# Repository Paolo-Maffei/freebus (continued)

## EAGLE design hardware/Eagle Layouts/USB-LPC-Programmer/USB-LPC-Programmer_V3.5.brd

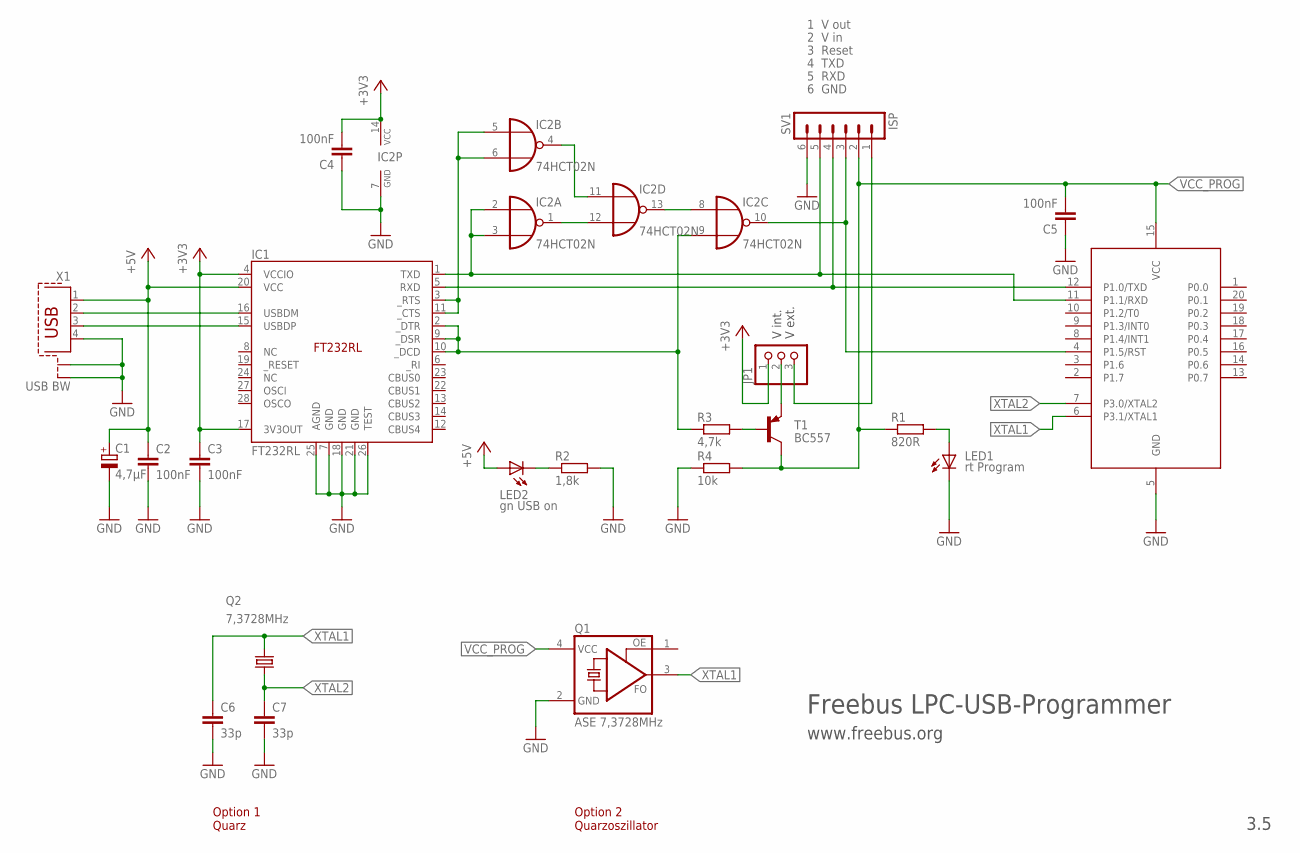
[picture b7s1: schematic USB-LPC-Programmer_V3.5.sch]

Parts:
89LPC922: LPC-Sockel; DIL20
C1: 4,7µF; E2,5-6
C2, C3, C4, C5: 100nF; C050-024X044
C6, C7: 33p; C025-024X044
IC1: FT232RL; SSOP-28
IC2: 74HCT02N; DIL14
JP1: PINHD-1X3; 1X03
LED1: rt Program; LED3MM
LED2: gn USB on; LED3MM
Q1: ASE 7,3728MHz; ASF
Q2: 7,3728MHz; HC49/S
R1: 820R; 0207/7
R2: 1,8k; 0207/7
R3: 4,7k; 0204/7
R4: 10k; 0207/7
SV1: ISP; MA06-1
T1: BC557; TO92
X1: USB BW; PN61729-S

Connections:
+3V3: C3.1, C4.2, IC1.4 (VCCIO), IC1.17 (3V3OUT), IC2.14 (VCC), JP1.1
+5V: C1.+, C2.1, IC1.20 (VCC), LED2.A, X1.1
GND: 89LPC922.5 (GND), C1.-, C2.2, C3.2, C4.1, C5.1, C6.2, C7.2, IC1.7 (GND), IC1.18 (GND), IC1.21 (GND), IC1.25 (AGND), IC1.26 (TEST), IC2.7 (GND), LED1.K (C), Q1.2 (GND), R2.2, R4.1, SV1.6, X1.4, X1.S1, X1.S2
unnamed: IC2.4 (O), IC2.11 (I0)
unnamed: JP1.2, T1.1 (E)
unnamed: 89LPC922.4 (P1.5/RST), IC2.10 (O), SV1.3
unnamed: JP1.3, SV1.1
unnamed: LED2.K (C), R2.1
unnamed: IC2.1 (O), IC2.12 (I1)
unnamed: LED1.A, R1.2
unnamed: IC1.16 (USBDM), X1.2
unnamed: IC2.8 (I0), IC2.13 (O)
unnamed: IC1.15 (USBDP), X1.3
unnamed: R3.2, T1.2 (B)
PROG_PWR_ON: IC1.2 (_DTR), IC1.9 (_DSR), IC1.10 (_DCD), IC2.9 (I1), R3.1
RTS_CTS1: IC1.3 (_RTS), IC1.11 (_CTS), IC2.5 (I0), IC2.6 (I1)
USB_RX: 89LPC922.12 (P1.0/TXD), IC1.5 (RXD), SV1.4
USB_TX: 89LPC922.11 (P1.1/RXD), IC1.1 (TXD), IC2.2 (I0), IC2.3 (I1), SV1.5
VCC_PROG: 89LPC922.15 (VCC), C5.2, Q1.4 (VCC), R1.1, R4.2, SV1.2, T1.3 (C)
XTAL1: 89LPC922.6 (P3.1/XTAL1), C6.1, Q1.3 (FO), Q2.2
XTAL2: 89LPC922.7 (P3.0/XTAL2), C7.1, Q2.1

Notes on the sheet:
Freebus LPC-USB-Programmer
www.freebus.org
3.5
2 V in
3 Reset
4 TXD
5 RXD
6 GND
1 V out
Option 1 Quarz
Option 2 Quarzoszillator
V int.
V ext.

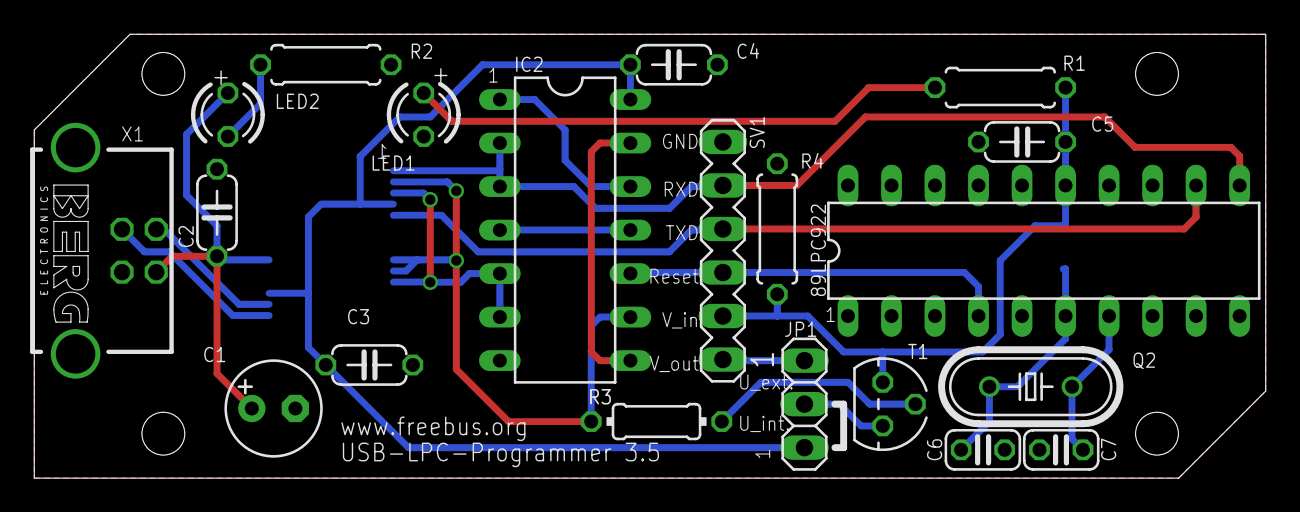
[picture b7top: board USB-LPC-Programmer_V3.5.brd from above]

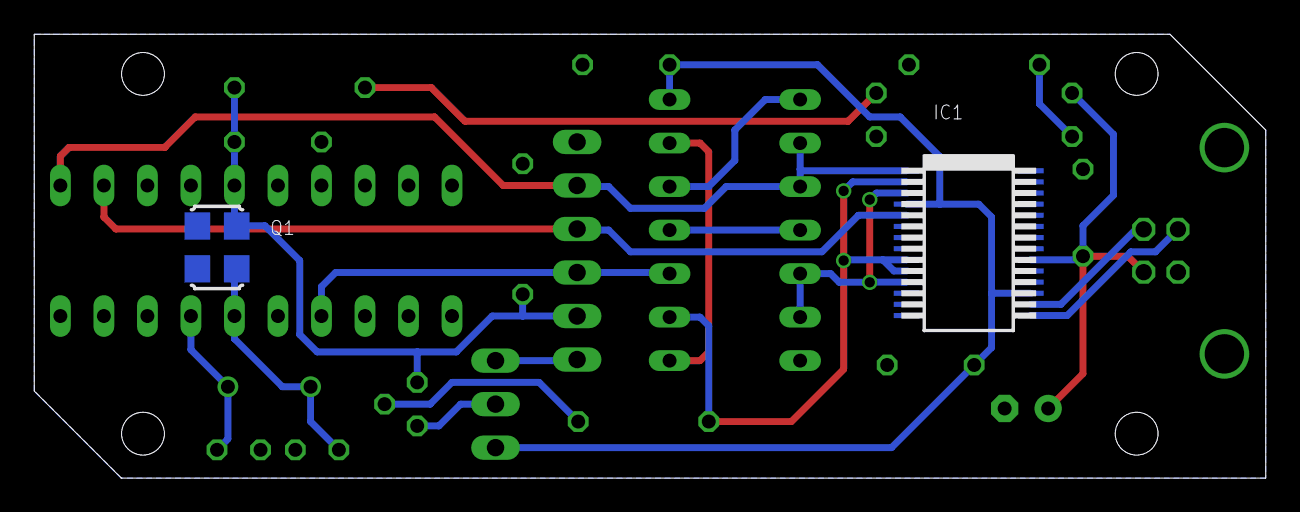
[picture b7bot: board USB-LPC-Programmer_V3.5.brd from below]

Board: 2 copper layers, 71.9 x 25.9 mm, 22 parts (2 on the bottom side), 21 nets.

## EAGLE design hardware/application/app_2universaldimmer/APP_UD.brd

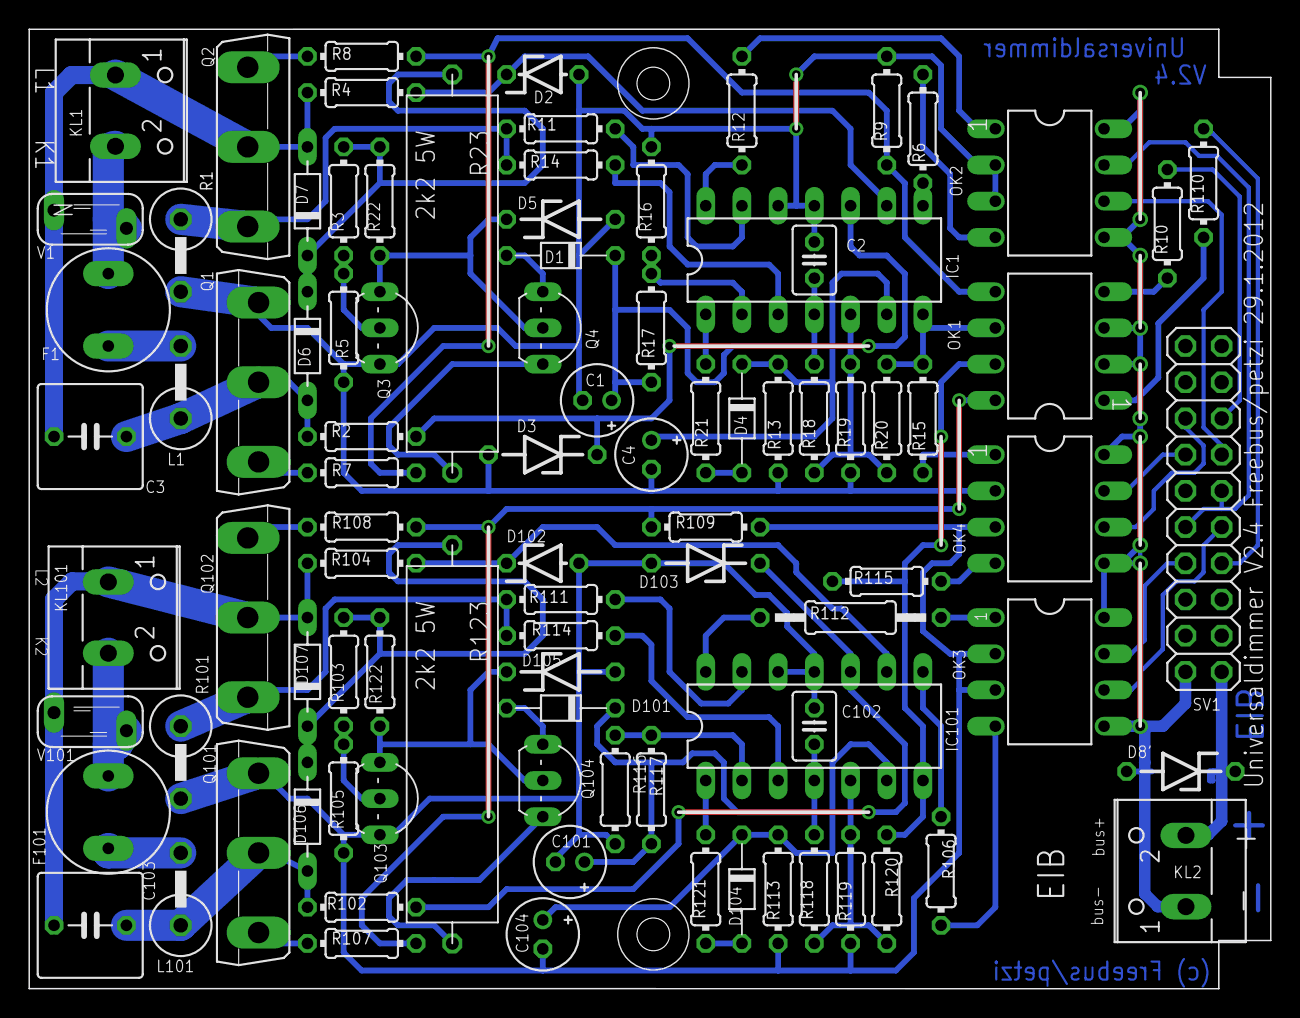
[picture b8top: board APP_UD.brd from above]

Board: 2 copper layers, 87.1 x 67.3 mm, 94 parts (1 on the bottom side), 72 nets.

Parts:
C1, C4, C101, C104: 47u; E2-5
C2, C102: 100n; C025-030X050
C3, C103: 6.8nF; C050-075X075
D1, D101: 1N4007; D-7
D2, D102: ZF6.8; ZDIO-5
D3, D103: ZF6.8; ZDIO-7.5
D4, D104: 1N4148; D-7
D5, D105: ZF15; ZDIO-7.5
D6, D7, D106, D107: 1N4007; D-7.5
D8: SMAJ40CA; SMBJ
D8': P6KE39A; ZDIO-7.5
F1, F101: 2A; TR5
IC1, IC101: LM324N; DIL14
KL1, KL2, KL101: W237-102
L1, L101: 3uH; 0414V
OK1, OK2, OK3, OK4: ILD74; DIL08
Q1, Q2, Q101, Q102: IRFP460; TO247BV
Q3, Q103: BC546B; TO92-EBC
Q4, Q104: MPSA44; TO92-EBC
R1, R101: 0,1; 0414V
R2, R4, R12, R13, R14, R18, R19, R22, R102, R104, R113, R114, R118, R119, R122: 100k; 0204/7
R3, R103: 4M3; 0204/7
R5, R9, R20, R105, R109, R120: 22k; 0204/7
R6, R106: 5k6; 0204/7
R7, R8, R10, R107, R108, R110: 1k; 0204/7
R11, R111: 100; 0204/7
R15, R115: 12k; 0204/7
R16, R116: 3k9; 0204/7
R17, R117: 220k; 0204/7
R21, R121: 470; 0204/7
R23, R123: 2k2 5W; KH208-8_10B
R112: 100k; 0207/12
SV1: 2X10
V1, V101: 7N391K; S05K11

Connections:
AGND1: C1.-, C2.2, C4.-, D2.A, D3.A, D5.A, IC1.11, IC1.12, OK2.2, OK2.3, OK4.2, Q1.S, Q3.E, R1.2, R5.1, R9.2, R13.2, R16.2, R19.1
AGND2: C101.-, C102.2, C104.-, D102.A, D103.A, D105.A, IC101.11, IC101.12, OK3.2, OK3.3, OK4.3, Q101.S, Q103.E, R101.2, R105.1, R109.2, R113.2, R116.2, R119.2
GND: D8.A, D8'.A, KL2.1, OK1.2, OK1.3, OK2.5, OK2.8, OK3.5, OK3.8, OK4.5, OK4.8, SV1.2
unnamed: R10.1, SV1.15
unnamed: OK1.4, R10.2
unnamed: C3.1, D6.A, L1.1, Q1.D, R2.1
unnamed: Q2.S, R1.1, R11.2, R14.2
unnamed: OK2.6, SV1.13
unnamed: IC1.7, OK1.6, R15.2, R20.1
unnamed: OK2.7, SV1.10, SV1.11
unnamed: F1.1, KL1.2, V1.2
unnamed: Q2.G, R8.2
unnamed: OK1.1, R110.2
unnamed: IC1.3, R14.1
unnamed: D6.C, D7.C, R3.2, R22.2, R23.P$1
unnamed: OK2.4, R6.1
unnamed: IC101.7, OK1.7, R115.2, R120.2
unnamed: IC1.8, R6.2
unnamed: Q3.B, R3.1, R5.2
unnamed: Q1.G, R7.2
unnamed: C3.2, D7.A, KL1.1, Q2.D, R4.1, V1.1
unnamed: D8.C, D8'.C, KL2.2, SV1.1
unnamed: IC1.2, R16.1, R17.2
unnamed: F1.2, L1.2
unnamed: D3.C, IC1.10, R2.2
unnamed: D2.C, IC1.9, R4.2
unnamed: IC1.1, R21.2
unnamed: C103.2, D107.A, KL101.1, Q102.D, R104.1, V101.1
unnamed: OK3.1, R112.1
unnamed: OK2.1, R12.1
unnamed: C4.+, D4.C, IC1.6, R13.1
unnamed: D5.C, Q3.C, Q4.B, R22.1
unnamed: OK4.1, R15.1
unnamed: OK4.7, SV1.14
unnamed: IC1.5, R18.2, R19.2, R20.2
unnamed: Q4.C, R23.P$2
unnamed: OK1.8, R107.1, R108.1, R109.1
unnamed: Q102.S, R101.1, R111.2, R114.2
unnamed: Q102.G, R108.2
unnamed: D106.C, D107.C, R103.2, R122.2, R123.P$1
unnamed: D103.C, IC101.10, R102.2
unnamed: D102.C, IC101.9, R104.2
unnamed: OK3.4, R106.1
unnamed: IC101.8, R106.2
unnamed: D1.A, Q4.E
unnamed: IC1.14, R12.2
unnamed: Q103.B, R103.1, R105.2
unnamed: OK3.6, SV1.9
unnamed: OK3.7, SV1.8
unnamed: R110.1, SV1.7
unnamed: Q101.G, R107.2
unnamed: IC101.13, R111.1
unnamed: D105.C, Q103.C, Q104.B, R122.1
unnamed: IC101.3, R114.1
unnamed: IC101.2, R116.1, R117.2
unnamed: IC101.1, R121.2
unnamed: C104.+, D104.C, IC101.6, R113.1
unnamed: OK4.4, R115.1
unnamed: OK4.6, SV1.16
unnamed: Q104.C, R123.P$2
unnamed: D4.A, R21.1
unnamed: D104.A, R121.1
unnamed: IC101.5, R118.2, R119.1, R120.1
unnamed: D101.A, Q104.E
unnamed: OK1.5, R7.1, R8.1, R9.1
unnamed: F101.1, KL101.2, V101.2
unnamed: IC101.14, R112.2
unnamed: F101.2, L101.2
unnamed: IC1.13, R11.1
unnamed: C103.1, D106.A, L101.1, Q101.D, R102.1
V12-C1: C1.+, C2.1, D1.C, IC1.4, R17.1, R18.1
V12-C2: C101.+, C102.1, D101.C, IC101.4, R117.1, R118.1

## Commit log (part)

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2009-07-13 Vorschlag für Universaldimmer, mit microcap getestet als Diskussionsgrundlage
2009-07-15 Value für schutzdiode im empfang eingefügt, noch testen!
2009-07-21 Atmega faq odt Format
2009-07-25 BSD optimiert. bla bla bla
2009-08-02 Debug handbetätigung 2TE: Dioden waren falsch rum
2009-08-11 Version auf Steckbrett aufgebaut und getestet. Ansteuerung sowie Erkennung der Nulldurchgänge von Strom und Spannung funktionieren
2009-08-14 black and high resolution logo with transparent background
2009-08-16 REG Beschriftung als .pdf und .svn Datei für Inkscape
2009-08-16 app_avr_display erstellt für erste Versuche
2009-08-19 avr_glcd_mmc Bilder hochgeladen vom 1.Testaufbau
2009-08-20 File to hold manual for modification of WRT54GL and software installation on it to get an EIB LAN interface.
2009-08-24 Tool to automatically install required software on a WRT54GL.
2009-08-24 freebus broschüre für die expo
2009-08-28 Added some checks and useful output to the user.
2009-09-07 Updates on schematic.
2009-09-09 Update wrong link.
2009-09-11 4te frontplatten als odg
2009-09-12 Updated placement for UP version.
2009-09-14 C5 und C6 im Netzteil hinzugefuegt
2009-09-16 Taster_LED mit option Quarz
2009-09-20 Universaldimmer: Pullupwiderstaende entfernt
2009-09-21 programmer C-10V debug, quarz option
2009-09-22 Fingerprint UP für B&J
2009-09-25 Anpassung an apliboard 3.43
2009-10-01 neue Version: für Gehäuse (1551F) 50x35x15 liegt hinter dem Taster
2009-10-04 Universaldimmer Stückliste hinzugefügt
2009-10-11 Erster Entwurf für RFID_Reader Hardware
2009-10-13 Neues Layout
    Layout nach Hinweisen von idefix geaendert
    Platinenausschnitte jetzt am Platinenrand
2009-10-18 update- EIB voltage monitoring and temp sensor with KYT10
2009-10-20 angepaßtes Layout
    Layout aufgrund größerem C8 angepaßt
    größere Pads für L2
2009-10-21 2in_2out_2te
    -erster Entwurf
    -basiert auf 4out2te und 8in230V
2009-10-24 neus Boardlayout
    -Busanschluss oben rechts
    -74HC14 Beschaltung komplettiert
2009-10-25 Corrected wrong fuses for controller.
2009-10-28 Added comment to enable debugging for eibd.
2009-10-29 telegrammaufbau korrigiert !
2009-10-29 Moved fingerprint documentation
2009-11-04 Applikationssoftware fuer 2te_kombi_2in_2out
    -erste version
2009-11-10 Universaldimmer: Erste getestete Version 1.0
2009-11-10 Universaldimmer: aus Ideasin appication verschoben
2009-11-15 Netzteil 800mA mit Kurzschlussschutz. Langzeittests stehen noch aus. Läuft seit vier Wochen.
2009-11-22 layoutfehler masseschluß ausgebessert an einem R
2009-11-24 Import of skeleton for telegram analyser.
2009-11-25 Modifications on GUI.
2009-11-26 Final version for GUI.
2009-11-29 fehlehhafte Anbindung des 220k Widerstandes korrigiert
2009-12-03 LPC 2TE einlagig mit kleine Adapterplatine auf der quarz und 2 33pF C sind, ausserdem der protection widerstand vor dem Empfänger C (100nf) und LED-Taster Platine für Anzeige und Handbetätigung
2009-12-15 Ueberarbeitete Versionen
    Controller 2te
    -Serienwiderstand 10k eingefügt
    -Spannungsteiler vor FET an VCC (fest 1,2V)
    -Beschriftung angepasst
    Kombi 2in-2out
    -Beschriftung angepasst
2009-12-19 hab eine orientierungsmarke die als leiterbahn gedeutet werden könnte entfernt.
2009-12-20 2te_kombi_2in_2out
    Entwurf der Applikationsbeschreibung
2009-12-26 v.0.02 Schaltung komplett, allerdings noch ohne Routing
2009-12-26 Platinenlayout fertig gerouted
2009-12-30 Changed GUI build to arrays.
2009-12-31 Program can analyse now octets till crc octet.
2009-12-31 Remove compiled jar file.
2010-01-01 Can now handle telegrams with more then 4-bit data inside.
2010-01-02 Version bump for GUI.
2010-01-07 Added additional search path for ipkg.
2010-01-07 Universaldimmer: Aenderung I-Sensor, Netzteil, diverses Layout nicht vollständig!
2010-01-08 Universaldimmer: V1.1 Layout fertig
2010-01-08 Universaldimmer: Messung der Signale
2010-01-10 Added support for Edimax to the script.
2010-01-10 Added notes how to activate the crystal.
2010-01-12 debug spannungs regler 3r6 - 3k6 und 100mfd
2010-01-16 howto updated ...
2010-01-19 Updated link to wrt54gl firmware.
2010-01-24 4temp_2te
    ueberarbeiteter Entwurf der Schaltung und Platine
    - Positionen und Beschriftung angepasst
2010-01-26 4temp_2te
    ueberarbeiteter Entwurf der Schaltung und Platine
    - Leiterbahnbreite auf 16mil, Positionen angepasst
2010-01-30 Vorlage für 8 x230V avr eingefügt
2010-02-06 Universaldimmer: V1.2 kleine Anpassungen
2010-02-12 Add in svn-zugang link to SVN handbook. Added notes about username and password to WRT manual.
2010-02-14 initial version of schematic diagram and layout for zone terminal (Meldegruppenterminal) and a LED status display.
2010-02-14 4temp_2te
    Ueberarbeitung nach 1.Prototyp
    - fehlende V+ Verbindung an OK4 zugefuegt
2010-02-14 Kleinere Anpassung an günstiger verfügbare Bauteile
2010-02-18 Noch einmal Leiterbahnen geringfügig geändert
2010-02-23 bs-druck und massefläche geändert
2010-02-23 layer tnames bnames an für herstellung
2010-02-23 BS UPDATE ISP/VCC/GND
2010-02-26 Universaldimmer: ToDos ergänuz
2010-03-05 erster Schaltungsentwurf für GLCD
2010-03-08 MMC-Adapter erstellt für Anschluß an Hauptplatine Widerstandswerte an Hauptplatine angepasst
2010-03-10 Universaldimmer: R20 / R120 angepasst, Doku erweitert um Messungen
2010-03-16 Added note that firmware with 19200 baud must be used (thanks to mel reporting it).
2010-03-19 Universaldimmer: FET-Ansteuerung invertiert, jetzt bei Busspannungsausfall aus
2010-04-06 First suggestion for AVR LED Switch board to use with the 8-out board.
2010-04-09 Versionsnummer angepasst, fehlendes Routing ergänzt
2010-04-10 keine Ahnung was ich da mal geändert hab
2010-04-10 LED 2, 4, 6, 8 um 180° gedreht. Clearance Pad-Wire erhöht.
2010-04-11 alte Version mit RFM12 gelöscht
2010-04-14 Corrected schema to match current version of led-switch board.
2010-04-16 ups fast vergessen :-) mal ein 8fach in 24V DC im 2 TE Gehäuse. gemeinsamer GND, LED nur für IO 0-3
2010-04-19 first project files for ir-receiver added
2010-04-20 LED Platine 2TE mit shift Register und 8 LEDs
2010-05-01 Dimmer mit RC glied auf drain-source
2010-05-07 loch zum anbohren des Tasters und padflaechen für die LED eingefügt, sonst wie rev e
2010-05-07 LED platine für den dual controller
2010-05-11 Replaced bmp with jpeg picture. Bitte keine so großen Bilder ins Repo laden, ein jpeg reicht vollkommen!
2010-05-13 Applikation 16xout bei 24V, für externe relaise, gemeinsamer VDD+24 (ULN out)
2010-05-28 Bitte verwendet keine Umlaute in Dateinamen oder Verzeichnisnamen, das macht zwischen verschiedenen Betriebssystemen Probleme. Hab das jetzt mal korrigiert. Achtet bitte drauf, dass keiner mehr Umala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
    Danke Euch.
2010-05-28 Added datasheets and manuals which could be help full for other developers.
2010-05-31 The doxygen documentation is not created automatically anymore. To create the doxygen docu execute make docu. Cleanup of Makefiles for app-8-out and app-8-in.
2010-06-03 update SMPS- smaller elcos, 80kHz, works fine->target for SMD componets and UP application. draft for replacement of 150mH inductor (constant supply current during low pulse)- not yet tested!!- could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
2010-06-04 smd controller 4TE rev 4.04
2010-06-05 C9 redurced to 47nF, time constant 4ms
2010-06-07 USB - frebus interface mit galvanischer trennung, ft1.2 firmware
2010-06-11 aenderung der WIMA Rastermaße auf 10.2 wegen spannungsfestigkeit
2010-06-13 lpc 2te 3.5f überarbeitet
2010-06-17 massefläche hinzugefügt beidseitig
2010-06-19 verschiedene Einbaumodule(fuer Rollokasten Hohldecke usw..)
2010-06-20 Aussparung für Schraube zugefügt, Buspads verschoben
2010-06-23 pcb layout aenderung, antennenbuchse oben.
2010-06-30 Corrected size of PCB to match excatly into the REG4 case without screws, size 67x58.1mm.
2010-07-11 Added chapter to restore original firmware. First part is not finished yet, do not use the instruction to install the firmware, use the old version of the manual for this.
2010-07-17 Corrected Makefile and first packages for openwrt backfire.
2010-07-17 Updated docu for openwrt backfire.
2010-07-17 Fixed link to point to external server now.
2010-07-20 kleine anpassungen am umriss
2010-08-06 Schaltung zum messen der Spannung am Bus hinzugefügt.
2010-08-08 Some small modification on the schematic.
2010-08-08 Added avr studio project file. Ignore binary files in commits.
2010-08-10 Moved test to a subfolder.
2010-08-15 Upgrade to newer version. Compiles now without patches.
2010-08-22 - display board: use 1 to turn on led - application board: minor layout changes, use of PC845 instead of PC847
2010-09-06 Bestückungsdruck optimiert. Neues Routing. Masseflöche hinzugefügt.
2010-09-07 v1.1 mit masseflächen
2010-09-07 changes t-names, description
2010-09-23 Platinen um aus Gira 147700 einen 6Fach Taster zu bauen
2010-09-28 Schaltung an die Schaltung vom Radio-bedienteil angepasst
2010-11-07 massefläche repariert und up damit
2010-11-16 update und modifikation bs-druck
2010-11-26 herstellung der daten konzistenz
2010-11-26 8out 1-lagig zum selberätzen zugefügt
2010-12-26 Drahtverbindung GND-VSS eingezeichnet
2010-12-29 rs-232 interface for debugging (AVR)
2011-01-10 Add some more files to the ignore list.
2011-01-27 commit wegen datenkon.
2011-01-27 dimmer fuer troniktrafogehäuse zugefügt
2011-02-09 New idea for new hardware revision of AVR controller board.
2011-02-17 Updated to new version of backfire, that could fix the problem with WLAN but I have not tested it yet.
2011-02-19 Reichelt Warenkorb ergänzt
2011-02-22 Added a section to fix WLAN problems with WRT54GL. Could maybe removed with a newer version of openwrt.
2011-03-05 vd für ert30 mit sollwertobjekt
2011-03-10 - Unterputz-Raumtemperaturregler zur Montage hinter einer Blindabdeckung - erzeugt anhand der Raumtemperatur und Sollwerttemperatur Stellgrößen für einen Heizungsaktor - Regelalgorithmus: PI und 2Pun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
2011-03-13 Universaldimmer: kleinere Korrekturen
2011-04-17 2TE 3.6 mit Schutzdiode im Empfang, Resetschutzbeschaltung V3.7 FET ersetzt durch BC547 EMV Optimierung
2011-05-11 little changes on board
2011-05-23 optimierte Leiterbahn zur Antennenbuchse. R8 (Strombegrenzung MC34063) jetzt 2R2.
2011-06-09 UPDATE Silkscreen and some Choppers
2011-06-23 Controler für ganz oben, schafft platz für mehr Aplikation, ohne LEDs,Taster. Progled und taster auf Aplikation
2011-09-23 Soft- und Hardware für zyklisches Senden eines Drucksensors (FSR406) auf den KNX.
2012-01-08 Added a small version of the freebus logo, used for git web GUI.
2012-01-13 Universaldimmer: alte Bilder gelöscht
2012-01-13 Universaldimmer: alte Platine gelöscht
2012-01-13 dummy
2012-01-13 test utf-8
2012-01-15 VD file to be used for the PIR sensor of the AVR project.
2012-01-15 Hinweis wie der APP_UD.sch File zu bekommen ist
2012-01-18 Hinweis nicht mehr nötig, da GIT pus mit plink.exe tut (im Gegensatz zu TortoisePlink.exe)
2012-01-21 UD: unnötige Leiterbahn entfernt
2012-01-21 UD: Hinweis auf Eagleversion 6.1 , ist mit alter Version nicht lesbar
2012-02-10 Dimmer Produktdatenbank hinzugefügt
2012-02-16 veraltete datei gelöscht
2012-02-25 UD: BOM Kleinsicherung Link auf reichelt zugefügt, WK aktualisiert
2012-04-15 UD: Bauanleitung: Inbetriebnahme ergänzt
2012-05-11 UD: Dokumente erweitert
2012-08-03 First version of a manual, how to work with Git and Freebus.
2012-08-06 8-fach Binäreingang 230 V: Schematic: Bauteilwerte hinzugefügt
2012-08-12 first eagle layout of 1-wire gateway
2012-08-19 some pictures about the 1-wire interface
2012-09-27 Added calculation tables for 4-temp application posted on the forum from Tontechniker.
2012-10-04 Added data sheet for 74HC573 which is used for 8-out application board.
2013-03-02 Added picture for 24V usage.
2013-03-02 Version 3.5 des USB-LPC-Programmers hinzugefügt
2013-03-16 Beschreibung ergänzt, Quarzposition korrigiert
2013-03-26 Updated manual to work with Git Extensions instead of TortoiseGit. Reason for this change is the TortoiseGit seems to be buggy and Git Extensions is easier to understand.
2013-04-18 Added AVR Controller 2te
2013-06-02 Added crystal to print
2013-06-07 Upgrade datasheet for atmega168p to current one.
2013-10-13 Added picture AVR Controller 2te
2013-12-28 Added LPC Kombisensor V3.52 with crystal oscillator
2014-02-28 Added 2out_0-10V_2te
